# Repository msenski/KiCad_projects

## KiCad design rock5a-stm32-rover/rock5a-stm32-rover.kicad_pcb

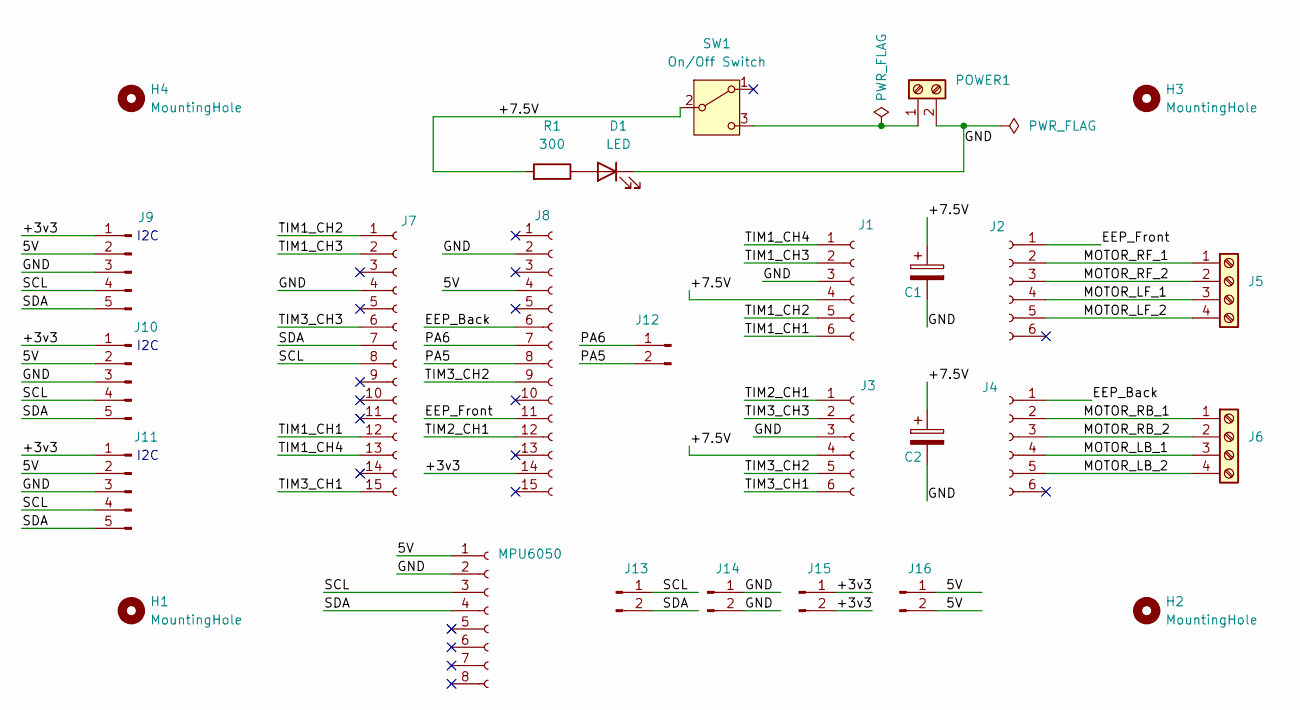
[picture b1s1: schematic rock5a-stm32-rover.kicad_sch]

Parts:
C1, C2: C_Polarized; CP_Radial_D6.3mm_P2.50mm
D1: LED; LED_D5.0mm
H1, H2, H3, H4: MountingHole; MountingHole_3.2mm_M3
J1, J3, J4: PinSocket_1x06_P2.54mm_Vertical
J2: Conn_01x06_Socket; PinSocket_1x06_P2.54mm_Vertical
J5, J6: Screw_Terminal_01x04; TerminalBlock_Phoenix_MKDS-1,5-4_1x04_P5.00mm_Horizontal
J7: G431KB Left; PinSocket_1x15_P2.54mm_Vertical
J8: G431KB Right; PinSocket_1x15_P2.54mm_Vertical
J9, J10, J11: Conn_01x05_Pin; PinSocket_1x05_P2.54mm_Vertical
J12, J13, J14, J15, J16: Conn_01x02_Pin; PinHeader_1x02_P2.54mm_Vertical
MPU6050: Conn_01x08_Socket; PinSocket_1x08_P2.54mm_Vertical
POWER1: Screw_Terminal_01x02; TerminalBlock_Phoenix_MKDS-1,5-2_1x02_P5.00mm_Horizontal
R1: 300; R_Bare_Metal_Element_L16.3mm_W4.8mm_P15.30mm
SW1: On/Off Switch; TerminalBlock_Phoenix_MKDS-1,5-3_1x03_P5.00mm_Horizontal

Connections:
/5V: J8.4 (+5V), J9.2 (+5V), J10.2 (+5V), J11.2 (+5V), J16.1, J16.2, MPU6050.1 (VIN)
/+3v3: J8.14 (+3v3), J9.1 (+3v3), J10.1 (+3v3), J11.1 (+3v3), J15.1, J15.2
/+7.5V: C1.1, C2.1, J1.4 (VCC), J3.4 (VCC), R1.2, SW1.2 (B)
/EEP_Back: J4.1 (EEP), J8.6 (PA7)
/EEP_Front: J2.1 (EEP), J8.11 (PA1)
/GND: C1.2, C2.2, D1.1 (K), J1.3 (GND), J3.3 (GND), J7.4 (GND), J8.2 (GND), J9.3 (GND), J10.3 (GND), J11.3 (GND), J14.1, J14.2, MPU6050.2 (GND), POWER1.2
/MOTOR_LB_1: J4.4 (OUT3), J6.3
/MOTOR_LB_2: J4.5 (OUT4), J6.4
/MOTOR_LF_1: J2.4 (OUT3), J5.3
/MOTOR_LF_2: J2.5 (OUT4), J5.4
/MOTOR_RB_1: J4.2 (OUT1), J6.1
/MOTOR_RB_2: J4.3 (OUT2), J6.2
/MOTOR_RF_1: J2.2 (OUT1), J5.1
/MOTOR_RF_2: J2.3 (OUT2), J5.2
/PA5: J8.8 (PA5), J12.2
/PA6: J8.7 (PA6), J12.1
/SCL: J7.8 (PA15), J9.4 (SCL), J10.4 (SCL), J11.4 (SCL), J13.1, MPU6050.3 (SCL)
/SDA: J7.7 (PB7), J9.5 (SDA), J10.5 (SDA), J11.5 (SDA), J13.2, MPU6050.4 (SDA)
/TIM1_CH1: J1.6 (IN1), J7.12 (PA8)
/TIM1_CH2: J1.5 (IN2), J7.1 (PA9)
/TIM1_CH3: J1.2 (IN3), J7.2 (PA10)
/TIM1_CH4: J1.1 (IN4), J7.13 (PA11)
/TIM2_CH1: J3.1 (IN4), J8.12 (PA0)
/TIM3_CH1: J3.6 (IN1), J7.15 (PB4)
/TIM3_CH2: J3.5 (IN2), J8.9 (PA4)
/TIM3_CH3: J3.2 (IN3), J7.6 (PB0)
unnamed: D1.2 (A), R1.1
unnamed: POWER1.1, SW1.3 (C)

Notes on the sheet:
I2C

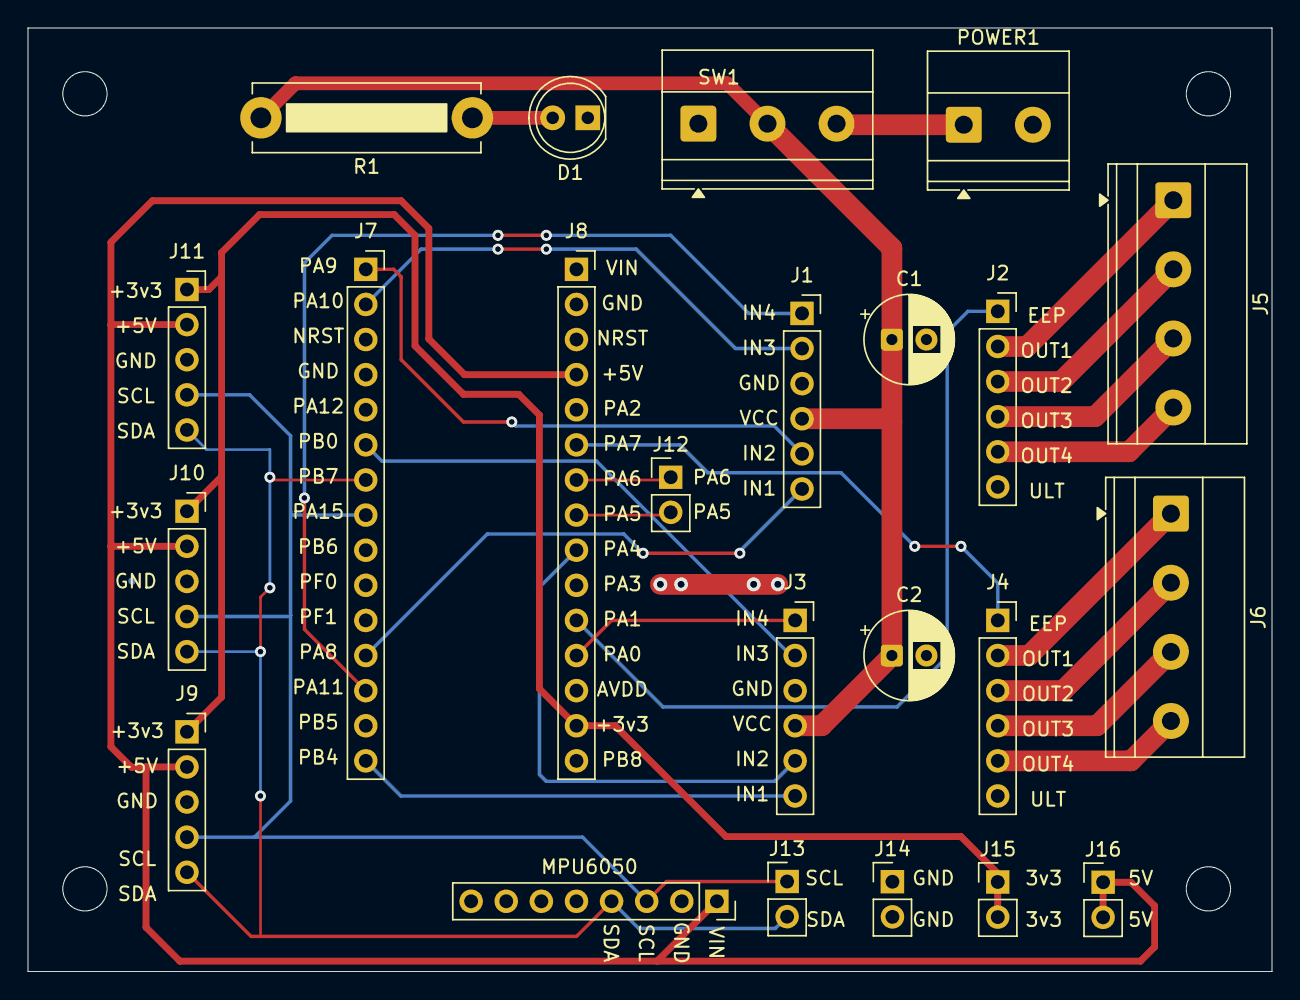
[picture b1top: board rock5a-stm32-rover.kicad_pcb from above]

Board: 2 copper layers, 90.0 x 68.3 mm, 27 parts (0 on the bottom side), 28 nets.
